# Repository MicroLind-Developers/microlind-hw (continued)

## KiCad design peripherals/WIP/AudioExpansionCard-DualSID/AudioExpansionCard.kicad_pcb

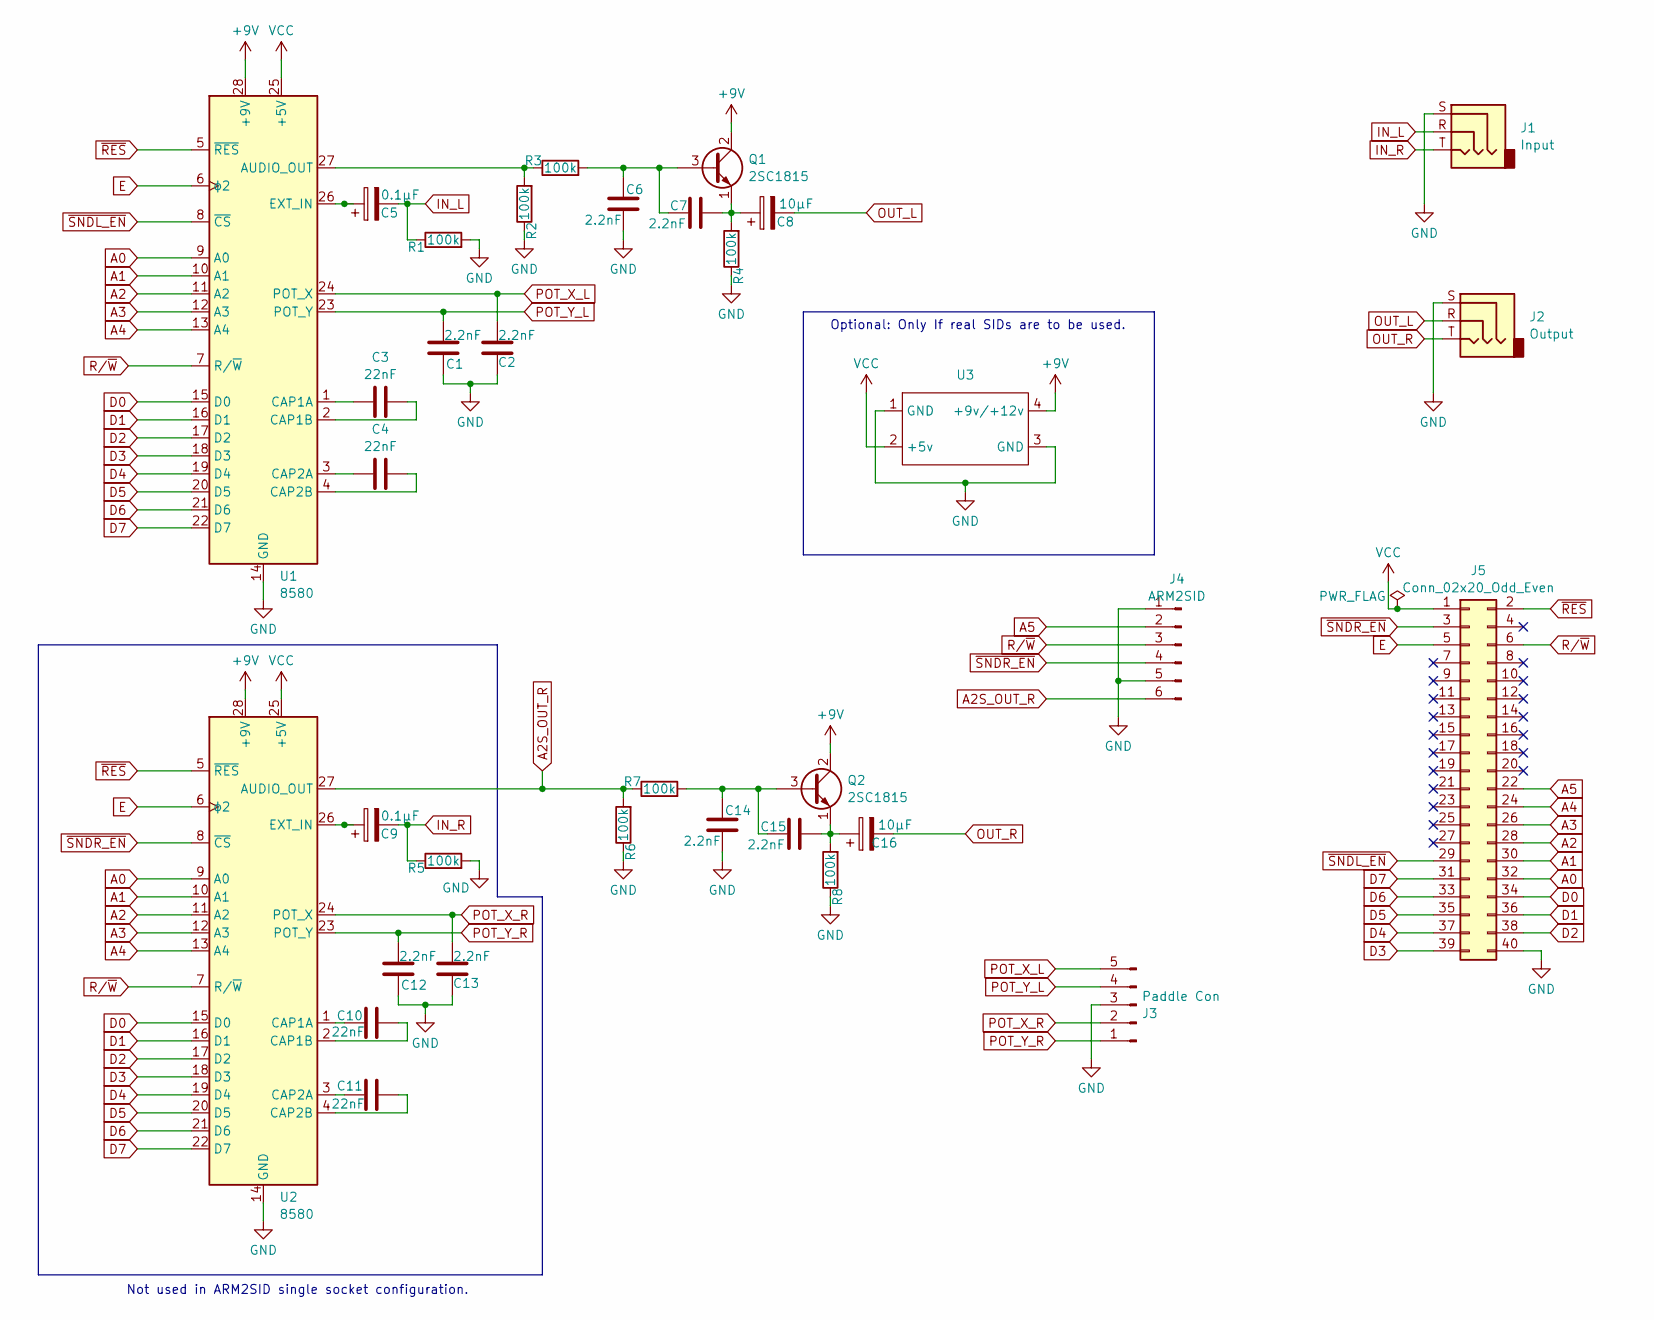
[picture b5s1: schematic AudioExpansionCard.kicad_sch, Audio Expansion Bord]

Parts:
C1, C2, C6, C7, C12, C13, C14, C15: 2.2nF; C_Disc_D3.0mm_W1.6mm_P2.50mm
C3, C4, C10, C11: 22nF; C_Disc_D3.0mm_W1.6mm_P2.50mm
C5, C9: 0.1µF; CP_Radial_D4.0mm_P1.50mm
C8, C16: 10µF; CP_Radial_D4.0mm_P1.50mm
J1: Input; Jack_3.5mm_CUI_SJ1-3533NG_Horizontal
J2: Output; Jack_3.5mm_CUI_SJ1-3533NG_Horizontal
J3: Paddle Con; PinHeader_1x05_P2.54mm_Horizontal
J4: ARM2SID; Molex_PicoBlade_53047-0610_1x06_P1.25mm_Vertical
J5: Conn_02x20_Odd_Even; AudioExpansionCard
Q1, Q2: 2SC1815; TO-92_Inline
R1, R2, R3, R4, R5, R6, R7, R8: 100k; R_Axial_DIN0207_L6.3mm_D2.5mm_P10.16mm_Horizontal
U1, U2: 8580; DIP-28_W15.24mm
U3: StepUpConverter

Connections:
+9V: Q1.2 (C), Q2.2 (C), U1.28 (+9V), U2.28 (+9V), U3.4 (+9v/+12v)
A0: J5.32, U1.9 (A0), U2.9 (A0)
A1: J5.30, U1.10 (A1), U2.10 (A1)
A2: J5.28, U1.11 (A2), U2.11 (A2)
A2S_OUT_R: J4.6, R6.2, R7.1, U2.27 (AUDIO_OUT)
A3: J5.26, U1.12 (A3), U2.12 (A3)
A4: J5.24, U1.13 (A4), U2.13 (A4)
A5: J4.2, J5.22
D0: J5.34, U1.15 (D0), U2.15 (D0)
D1: J5.36, U1.16 (D1), U2.16 (D1)
D2: J5.38, U1.17 (D2), U2.17 (D2)
D3: J5.39, U1.18 (D3), U2.18 (D3)
D4: J5.37, U1.19 (D4), U2.19 (D4)
D5: J5.35, U1.20 (D5), U2.20 (D5)
D6: J5.33, U1.21 (D6), U2.21 (D6)
D7: J5.31, U1.22 (D7), U2.22 (D7)
E: J5.5, U1.6 (ϕ2), U2.6 (ϕ2)
GND: C1.2, C2.2, C6.2, C12.2, C13.2, C14.2, J1.S, J2.S, J3.3, J4.1, J4.5, J5.40, R1.2, R2.1, R4.1, R5.2, R6.1, R8.1, U1.14 (GND), U2.14 (GND), U3.1 (GND), U3.3 (GND)
IN_L: C5.2, J1.R, R1.1
IN_R: C9.2, J1.T, R5.1
unnamed: C6.1, C7.1, Q1.3 (B), R3.2
unnamed: C7.2, C8.1, Q1.1 (E), R4.2
unnamed: C14.1, C15.1, Q2.3 (B), R7.2
unnamed: C15.2, C16.1, Q2.1 (E), R8.2
unnamed: R2.2, R3.1, U1.27 (AUDIO_OUT)
unnamed: C3.1, U1.1 (CAP1A)
unnamed: C3.2, U1.2 (CAP1B)
unnamed: C4.1, U1.3 (CAP2A)
unnamed: C4.2, U1.4 (CAP2B)
unnamed: C5.1, U1.26 (EXT_IN)
unnamed: C10.1, U2.1 (CAP1A)
unnamed: C10.2, U2.2 (CAP1B)
unnamed: C11.1, U2.3 (CAP2A)
unnamed: C11.2, U2.4 (CAP2B)
unnamed: C9.1, U2.26 (EXT_IN)
OUT_L: C8.2, J2.R
OUT_R: C16.2, J2.T
POT_X_L: C2.1, J3.5, U1.24 (POT_X)
POT_X_R: C13.1, J3.2, U2.24 (POT_X)
POT_Y_L: C1.1, J3.4, U1.23 (POT_Y)
POT_Y_R: C12.1, J3.1, U2.23 (POT_Y)
R/~W: J4.3, J5.6, U1.7 (R/~W), U2.7 (R/~W)
VCC: J5.1, U1.25 (+5V), U2.25 (+5V), U3.2 (+5v)
~RES: J5.2, U1.5 (~RES), U2.5 (~RES)
~SNDL_EN: J5.29, U1.8 (~CS)
~SNDR_EN: J4.4, J5.3, U2.8 (~CS)

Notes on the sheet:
Not used in ARM2SID single socket configuration.
Optional: Only If real SIDs are to be used.

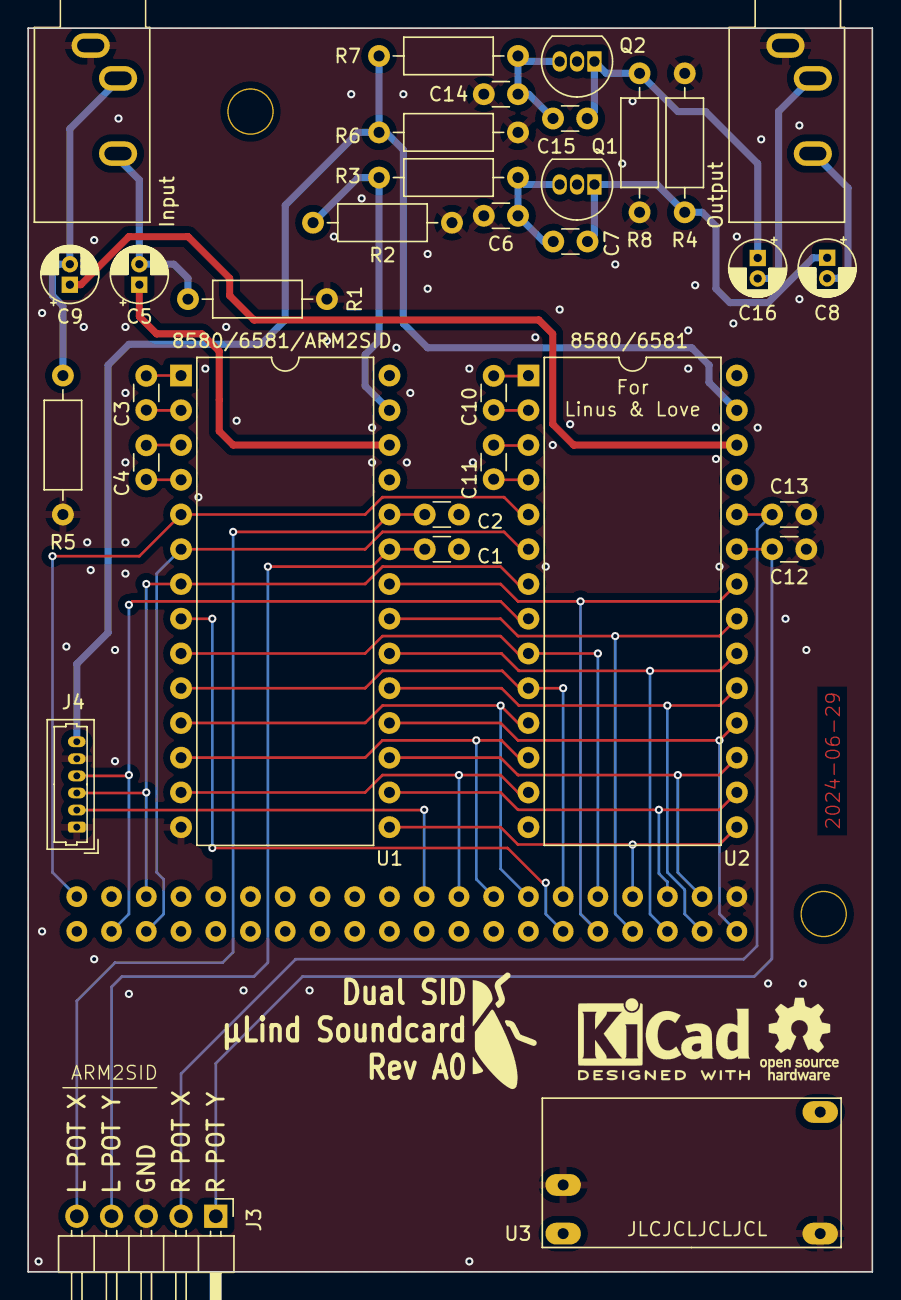
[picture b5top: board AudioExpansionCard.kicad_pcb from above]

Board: 4 copper layers, 61.7 x 90.9 mm, 34 parts (0 on the bottom side), 46 nets.

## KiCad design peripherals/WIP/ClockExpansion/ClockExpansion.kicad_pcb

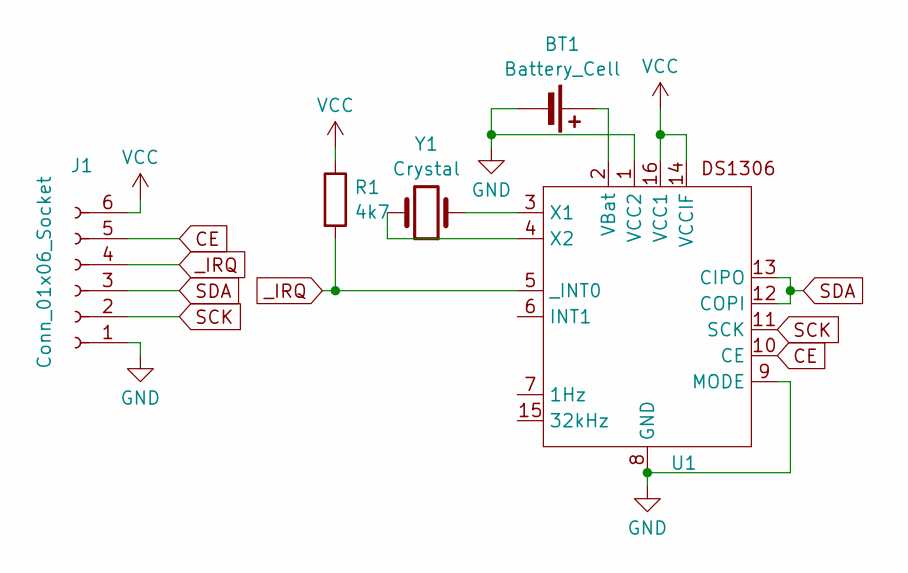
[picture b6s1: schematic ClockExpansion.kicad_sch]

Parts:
BT1: Battery_Cell; BatteryHolder_Keystone_3001_1x12mm
J1: Conn_01x06_Socket; PinSocket_1x06_P2.54mm_Horizontal
R1: 4k7; R_Axial_DIN0411_L9.9mm_D3.6mm_P12.70mm_Horizontal
U1: DIP-16_W7.62mm
Y1: Crystal; Crystal_C26-LF_D2.1mm_L6.5mm_Horizontal

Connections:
CE: J1.5, U1.10 (CE)
GND: BT1.2 (-), J1.1, U1.1 (VCC2), U1.8 (GND), U1.9 (MODE)
unnamed: BT1.1 (+), U1.2 (VBat)
unnamed: U1.3 (X1), Y1.1
unnamed: U1.4 (X2), Y1.2
SCK: J1.2, U1.11 (SCK)
SDA: J1.3, U1.12 (COPI), U1.13 (CIPO)
VCC: J1.6, R1.1, U1.14 (VCCIF), U1.16 (VCC1)
_IRQ: J1.4, R1.2, U1.5 (_INT0)

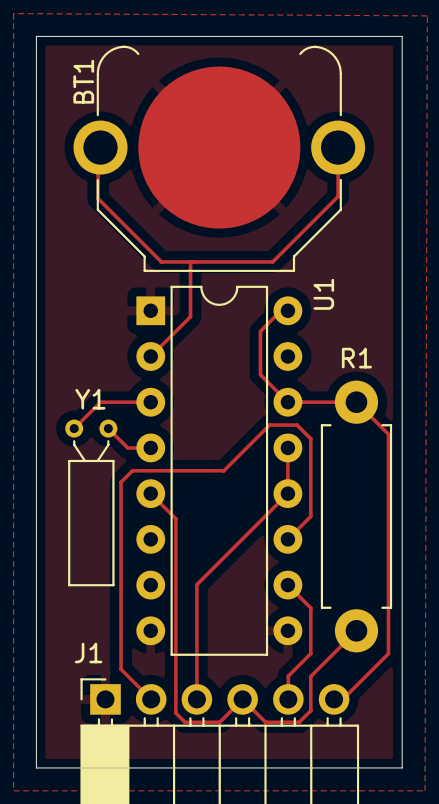
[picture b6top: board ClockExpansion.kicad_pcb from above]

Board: 2 copper layers, 20.3 x 40.6 mm, 5 parts (0 on the bottom side), 9 nets.

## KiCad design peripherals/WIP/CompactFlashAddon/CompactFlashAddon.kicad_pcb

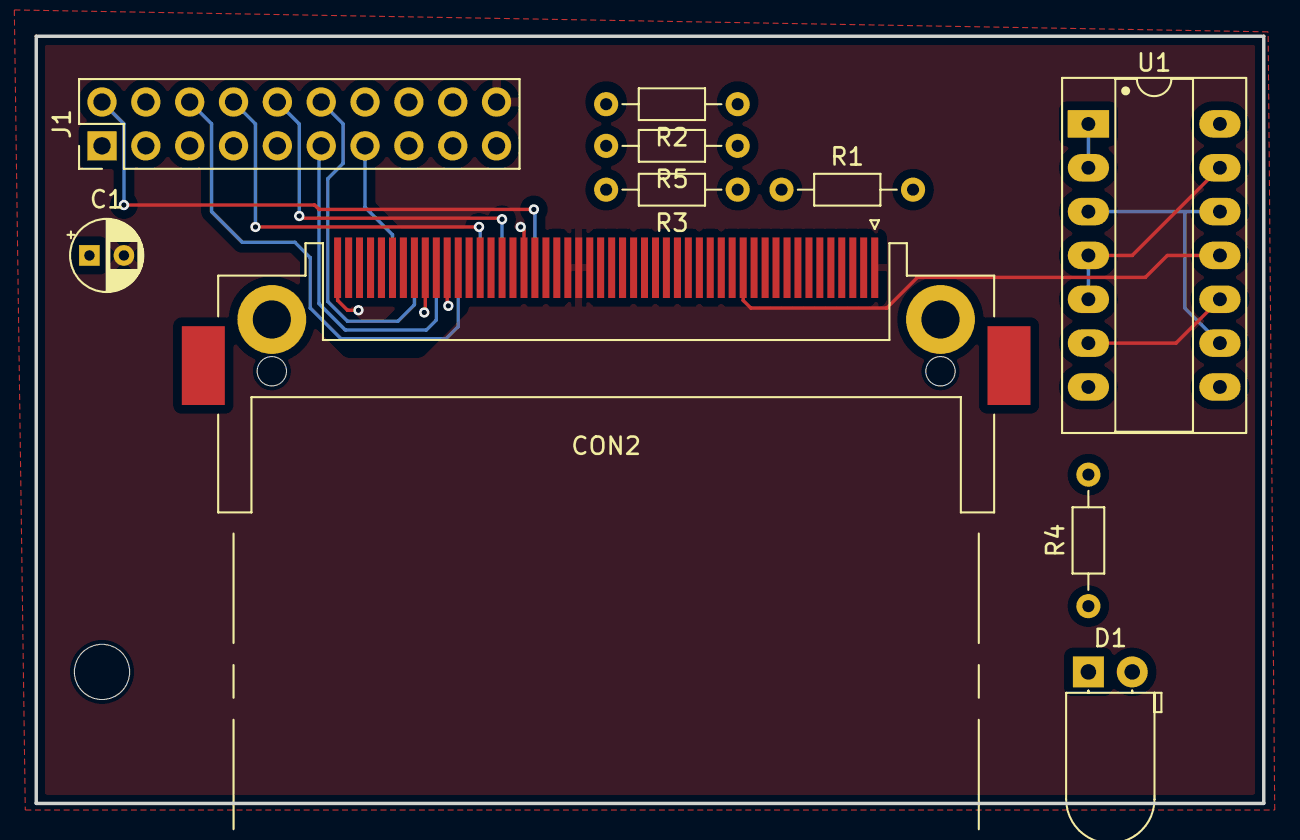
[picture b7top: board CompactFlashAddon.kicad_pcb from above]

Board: 2 copper layers, 71.1 x 44.4 mm, 10 parts (0 on the bottom side), 27 nets.

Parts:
C1: C_Polarized; CP_Radial_D4.0mm_P2.00mm
CON2: CF-CARD; CF-Card_3M_N7E50-7516PK-20-WF
D1: LED; LED_D5.0mm_Horizontal_O1.27mm_Z3.0mm_Clear
J1: CompactFlashAddon; PinHeader_2x10_P2.54mm_Vertical
R1, R2, R3, R4, R5: 4k7; R_Axial_DIN0204_L3.6mm_D1.6mm_P7.62mm_Horizontal
U1: 74HCT00; DIP-14_W7.62mm_Socket_LongPads

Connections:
/A0: CON2.20 (A0), J1.6
/A1: CON2.19 (A1), J1.8
/A2: CON2.18 (A2), J1.10
/D0: CON2.21 (D0), J1.11
/D1: CON2.22 (D1), J1.12
/D2: CON2.23 (D2), J1.13
/D3: CON2.2 (D3), J1.14
/D4: CON2.3 (D4), J1.15
/D5: CON2.4 (D5), J1.16
/D6: CON2.5 (D6), J1.17
/D7: CON2.6 (D7), J1.18
/~CF_EN: J1.7, R1.2, U1.1, U1.2
/~RD: CON2.34 (/IORD), J1.5
/~RST: CON2.41 (/RESET), J1.2
/~WR: CON2.35 (/IOWR), J1.4
A3: J1.9, U1.4, U1.5, U1.13
GND: C1.2, CON2.1 (GND1), CON2.8 (A10), CON2.9 (/ATASEL), CON2.10 (A9), CON2.11 (A8), CON2.12 (A7), CON2.14 (A6), CON2.15 (A5), CON2.16 (A4), CON2.17 (A3), CON2.39 (/CSEL), CON2.50 (GND2), J1.20
unnamed: CON2.7 (/CS0), U1.11
unnamed: CON2.32 (/CS1), U1.8
unnamed: CON2.45 (/DASP), R4.2
unnamed: CON2.46 (/PDIAG), R5.2
unnamed: CON2.44 (/REG), R3.2
unnamed: CON2.36 (/WE), R2.2
unnamed: D1.2 (A), R4.1
unnamed: U1.6, U1.10
unnamed: U1.3, U1.9, U1.12
VCC: C1.1, CON2.13 (VCC2), CON2.38 (VCC1), D1.1 (K), J1.1, R1.1, R2.1, R3.1, R5.1
